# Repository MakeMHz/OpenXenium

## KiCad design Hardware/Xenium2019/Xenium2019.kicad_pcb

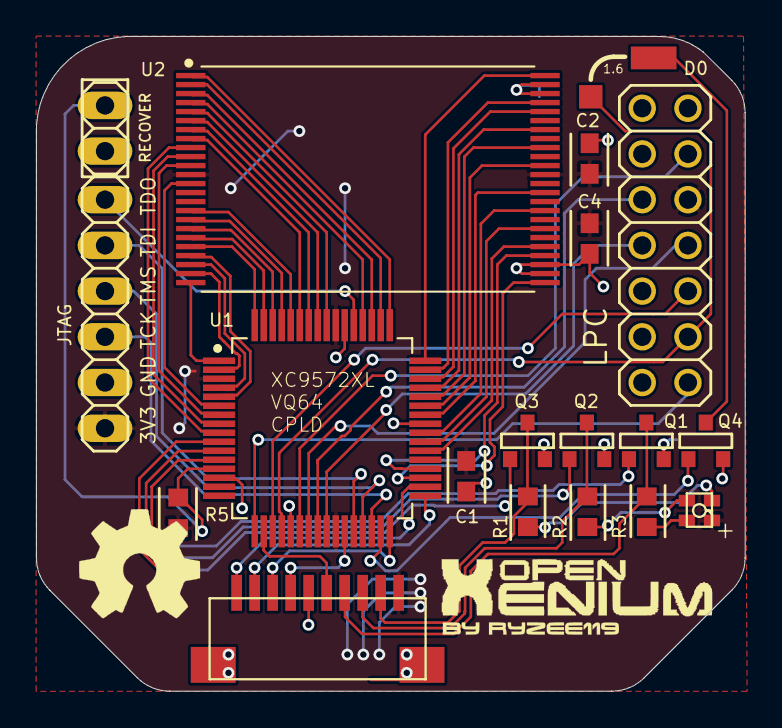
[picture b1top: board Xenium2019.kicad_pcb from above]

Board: 2 copper layers, 39.4 x 36.4 mm, 20 parts (0 on the bottom side), 62 nets.

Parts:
C1, C2: 100n; C0603
C4: 10u; C0603
D0: SMD2; SMD1,27-2,54
J1: SM10B-SRSS-TB
JTAG: PINHD-1X6; 1X06
L1: 19-237_R6GHBHC-A07_2T; 4-SMD-R6GHBHC
LPC: PINHD-2X7; 2X07
Q1, Q2, Q3, Q4: 310mA/60V/1.6Ω; SOT-23
R1, R2, R3: 68; R0603
R5: 1k; R0603
RECOVERY1: PINHD-1X2; 1X02
TP1: TPTP13SQ; TP13SQ
U1: XC9572XL-10VQG64; LQFP64
U2: AM29LV160M; TSOP48

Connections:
+3V3: C1.1, C2.1, C4.1, J1.10, JTAG.1, L1.P$2, LPC.9, R5.2, U1.3, U1.26, U1.37, U1.55, U2.12, U2.37
/A0: U1.35, U2.25
/A1: U1.1, U2.24
/A2: U1.2, U2.23
/A3: U1.4, U2.22
/A4: U1.5, U2.21
/A5: U1.64, U2.20
/A6: U1.63, U2.19
/A7: U1.62, U2.18
/A8: U1.59, U2.8
/A9: U1.58, U2.7
/A10: U1.57, U2.6
/A11: U1.56, U2.5
/A12: U1.52, U2.4
/A13: U1.51, U2.3
/A14: U1.50, U2.2
/A15: U1.49, U2.1
/A16: U1.48, U2.48
/A17: U1.61, U2.17
/A18: U1.60, U2.16
/A19: U1.9, U2.9
/A-1: U1.47, U2.45
/B: Q3.3, U1.10
/B_EXT: J1.9, Q3.1, R1.2
/CS: J1.6, U1.18
/DQ0: U1.38, U2.29
/DQ1: U1.39, U2.31
/DQ2: U1.40, U2.33
/DQ3: U1.42, U2.35
/DQ4: U1.43, U2.38
/DQ5: U1.44, U2.40
/DQ6: U1.45, U2.42
/DQ7: U1.46, U2.44
/G: Q2.3, U1.11
/G_EXT: J1.8, Q2.1, R2.2
/INPUT: J1.4, U1.27
/LAD0: LPC.11, U1.22
/LAD1: LPC.10, U1.24
/LAD2: LPC.8, U1.25
/LAD3: LPC.7, U1.23
/LCLK: LPC.1, U1.17
/LFRAME: LPC.3, TP1.TP, U1.20
/MISO: J1.1, U1.34
/MOSI: J1.2, U1.33
/NC: U1.6, U2.13
/NC_2: U1.8, U2.10
/R: Q1.3, U1.12
/RECOVER: R5.1, RECOVERY1.2, U1.13
/RST: LPC.5, U1.19
/R_EXT: J1.7, Q1.1, R3.2
/SCK: J1.3, U1.32
/TCK: JTAG.3, U1.30
/TDI: JTAG.5, U1.28
/TDO: JTAG.6, U1.53
/TMS: JTAG.4, U1.29
/~OE: U1.36, U2.28
/~WE: U1.7, U2.11
GND: C1.2, C2.2, C4.2, J1.5, J1.C1, J1.C2, JTAG.2, LPC.2, LPC.12, Q1.2, Q2.2, Q3.2, Q4.2, RECOVERY1.1, U1.14, U1.21, U1.41, U1.54, U2.26, U2.27, U2.46, U2.47
unnamed: D0.1, Q4.1
unnamed: L1.P$1, R3.1
unnamed: L1.P$3, R2.1
unnamed: Q4.3, U1.31

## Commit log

2020-09-09 Straighten out top edge of PCB
2020-09-10 Initial conversion
2020-09-10 Panel v1
